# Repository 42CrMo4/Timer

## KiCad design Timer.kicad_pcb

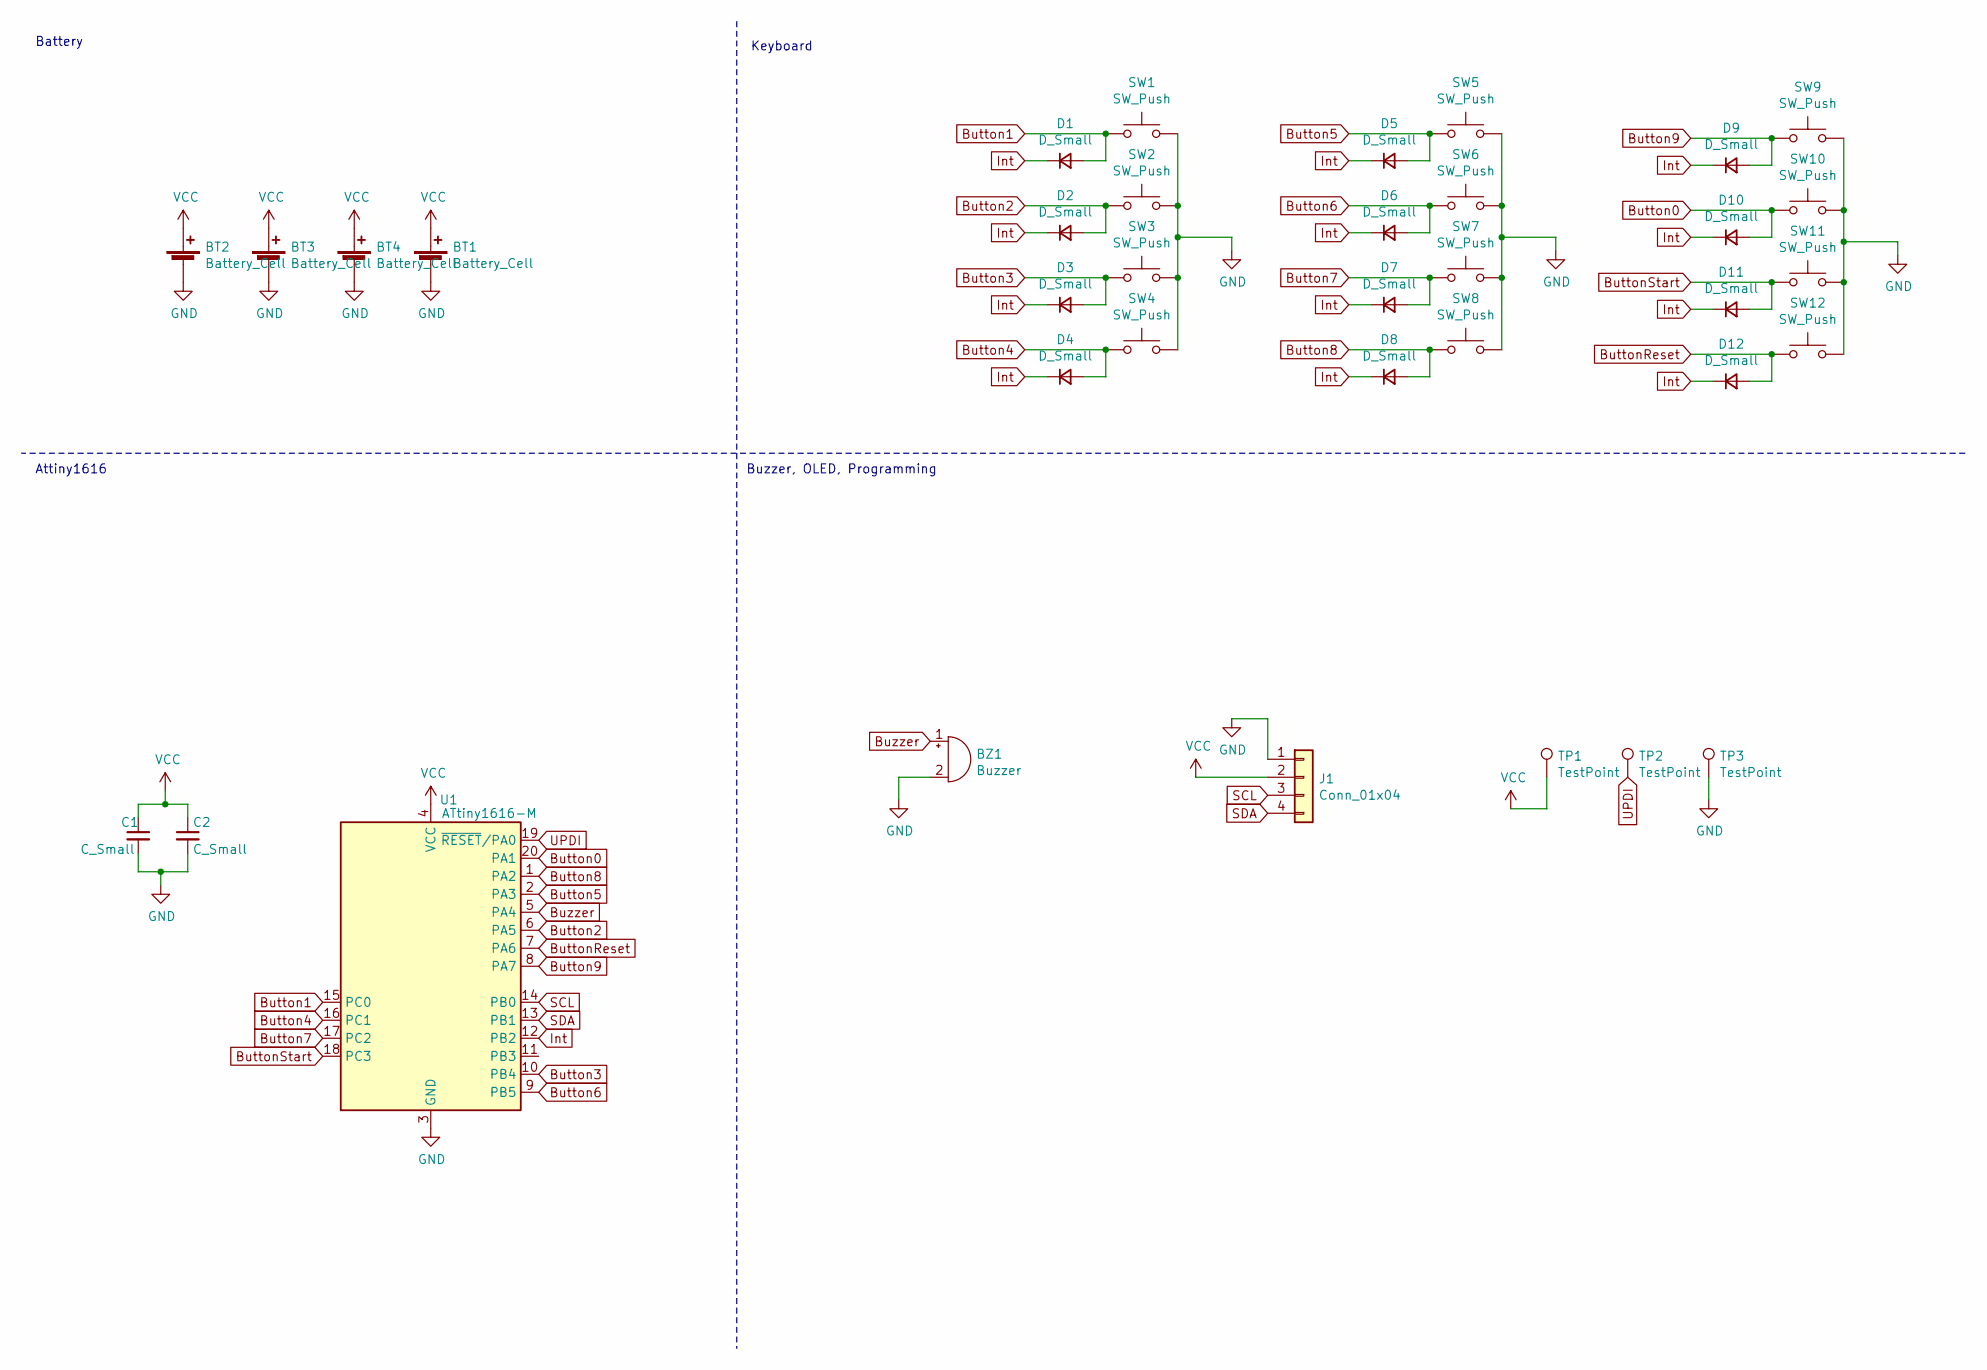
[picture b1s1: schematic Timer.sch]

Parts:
BT1, BT2, BT3, BT4: Battery_Cell; BatteryHolder_3DPrint_1xAAA
BZ1: Buzzer; Buzzer_12x9.5RM7.6
C1, C2: C_Small; C_0805_2012Metric
D1, D2, D3, D4, D5, D6, D7, D8, D9, D10, D11, D12: D_Small; D_0805_2012Metric
J1: Conn_01x04; PinHeader_1x04_P2.54mm_Vertical
SW1, SW2, SW3, SW4, SW5, SW6, SW7, SW8, SW9, SW10, SW11, SW12: SW_Push; SW_Cherry_MX_1.00u_PCB
TP1, TP2, TP3: TestPoint; TestPoint_Pad_D1.5mm
U1: ATtiny1616-M; VQFN-20-1EP_3x3mm_P0.4mm_EP1.7x1.7mm

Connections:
Button0: D10.2 (A), SW10.1, U1.20 (PA1)
Button1: D1.2 (A), SW1.1, U1.15 (PC0)
Button2: D2.2 (A), SW2.1, U1.6 (PA5)
Button3: D3.2 (A), SW3.1, U1.10 (PB4)
Button4: D4.2 (A), SW4.1, U1.16 (PC1)
Button5: D5.2 (A), SW5.1, U1.2 (PA3)
Button6: D6.2 (A), SW6.1, U1.9 (PB5)
Button7: D7.2 (A), SW7.1, U1.17 (PC2)
Button8: D8.2 (A), SW8.1, U1.1 (PA2)
Button9: D9.2 (A), SW9.1, U1.8 (PA7)
ButtonReset: D12.2 (A), SW12.1, U1.7 (PA6)
ButtonStart: D11.2 (A), SW11.1, U1.18 (PC3)
Buzzer: BZ1.1 (-), U1.5 (PA4)
GND: BT1.2 (-), BT2.2 (-), BT3.2 (-), BT4.2 (-), BZ1.2 (+), C1.2, C2.2, J1.1, SW1.2, SW2.2, SW3.2, SW4.2, SW5.2, SW6.2, SW7.2, SW8.2, SW9.2, SW10.2, SW11.2, SW12.2, TP3.1, U1.3 (GND), U1.21 (GND)
Int: D1.1 (K), D2.1 (K), D3.1 (K), D4.1 (K), D5.1 (K), D6.1 (K), D7.1 (K), D8.1 (K), D9.1 (K), D10.1 (K), D11.1 (K), D12.1 (K), U1.12 (PB2)
SCL: J1.3, U1.14 (PB0)
SDA: J1.4, U1.13 (PB1)
UPDI: TP2.1, U1.19 (~RESET~/PA0)
VCC: BT1.1 (+), BT2.1 (+), BT3.1 (+), BT4.1 (+), C1.1, C2.1, J1.2, TP1.1, U1.4 (VCC)

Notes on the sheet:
Battery
Keyboard
Attiny1616
Buzzer, OLED, Programming

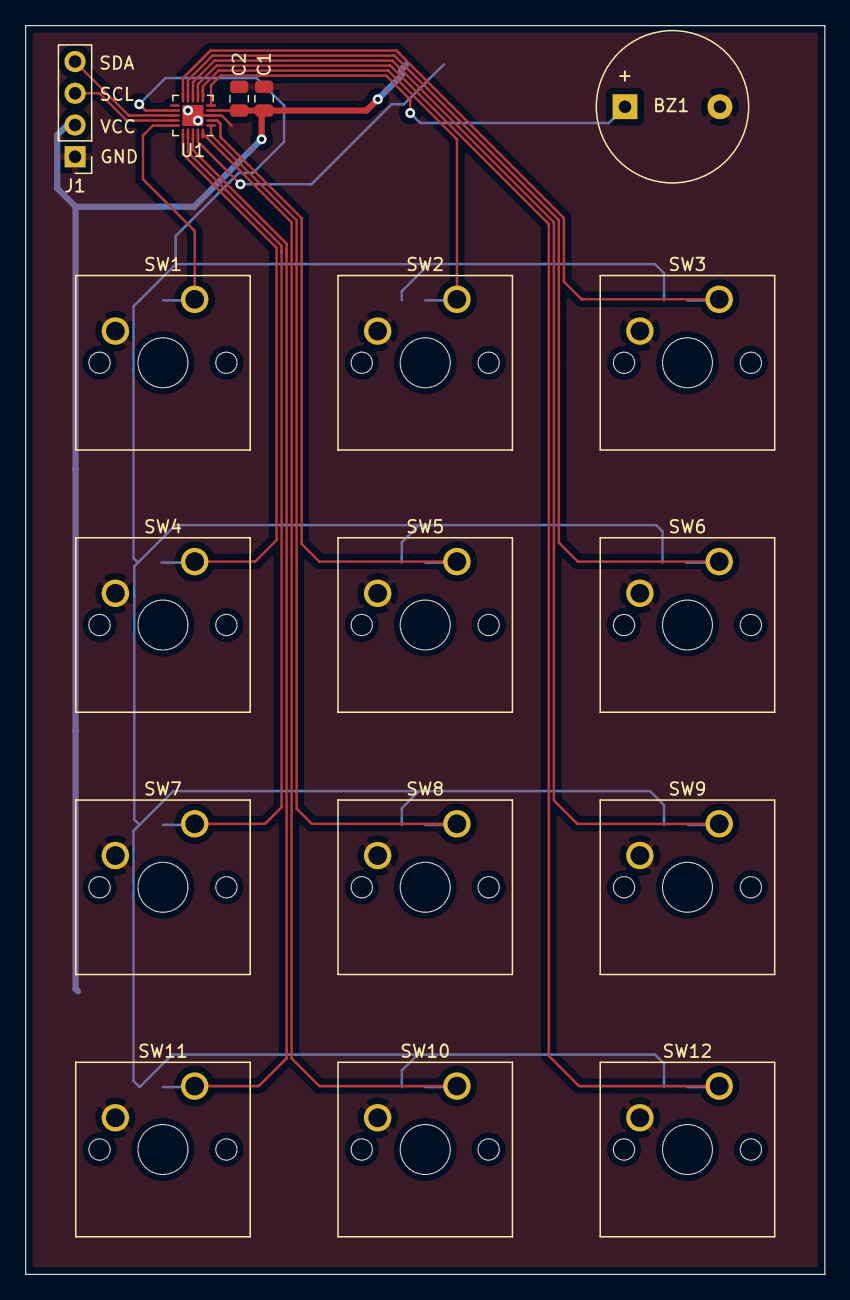
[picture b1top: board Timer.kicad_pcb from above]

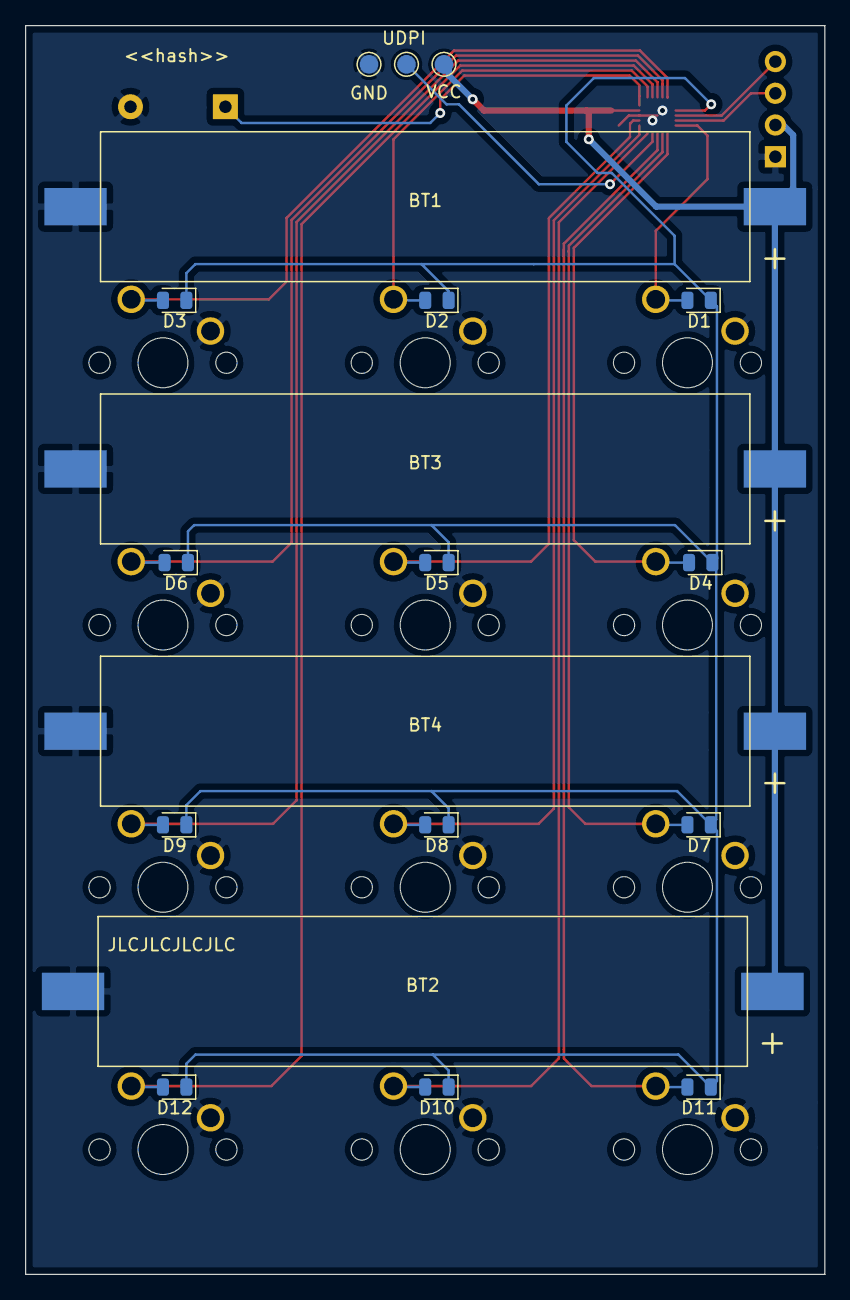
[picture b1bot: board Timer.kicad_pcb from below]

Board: 2 copper layers, 64.0 x 100.0 mm, 36 parts (19 on the bottom side), 19 nets.

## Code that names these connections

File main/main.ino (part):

#include <ezButton.h>
#include <tinyNeoPixel.h>
#define NUMLEDS 22
tinyNeoPixel leds = tinyNeoPixel(NUMLEDS, PIN_PB1, NEO_GRB);
int start_led = 0;

// Setup all Buttons
ezButton button1(PIN_PC0);
ezButton button2(PIN_PA5);
ezButton button3(PIN_PB4);
ezButton button4(PIN_PC1);
ezButton button5(PIN_PA3);
ezButton button6(PIN_PB5);
ezButton button7(PIN_PC2);
ezButton button8(PIN_PA2);
ezButton button9(PIN_PA7);
ezButton button0(PIN_PA1);
ezButton buttonStart(PIN_PC3);
ezButton buttonReset(PIN_PA6);

// int
int h1 = 0;
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
void setup() {
  // Pin configuration SetUp
  pinConfigure(PIN_PA1, (PIN_DIR_INPUT | PIN_PULLUP_ON));
  pinConfigure(PIN_PA2, (PIN_DIR_INPUT | PIN_PULLUP_ON));
  pinConfigure(PIN_PA3, (PIN_DIR_INPUT | PIN_PULLUP_ON));
  pinConfigure(PIN_PA5, (PIN_DIR_INPUT | PIN_PULLUP_ON));
  pinConfigure(PIN_PA6, (PIN_DIR_INPUT | PIN_PULLUP_ON));
  pinConfigure(PIN_PA7, (PIN_DIR_INPUT | PIN_PULLUP_ON));
  pinConfigure(PIN_PB4, (PIN_DIR_INPUT | PIN_PULLUP_ON));
  pinConfigure(PIN_PB5, (PIN_DIR_INPUT | PIN_PULLUP_ON));
  pinConfigure(PIN_PC0, (PIN_DIR_INPUT | PIN_PULLUP_ON));
  pinConfigure(PIN_PC1, (PIN_DIR_INPUT | PIN_PULLUP_ON));
  pinConfigure(PIN_PC2, (PIN_DIR_INPUT | PIN_PULLUP_ON));
  pinConfigure(PIN_PC3, (PIN_DIR_INPUT | PIN_PULLUP_ON));
  pinConfigure(PIN_PA4, (PIN_DIR_OUTPUT));

  delay(100);

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      countown_done = true;
      //      u8x8.clearDisplay();
      leds.clear();
//      digitalWrite(PIN_PA4, HIGH);
//      delay(500);
//      digitalWrite(PIN_PA4, LOW);
      countup();
    }
  }
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
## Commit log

2021-09-25 add SCH/PCB/Req
2021-09-26 add requirements
2021-09-26 add workflow
2021-09-26 test to trigger WF
2021-09-26 update path in WF
2021-09-27 add kiplot file
2021-09-27 WF without path
2021-09-27 WF with Path
2021-09-27 add pcbdraw to WF
2021-09-29 add Silkscreen move Testpoints
2021-09-29 update gnd fill
2021-10-13 add simple Test Sketch
2021-10-13 add oled Test sketch with U8g2
2021-10-13 add timer Sketch
2021-10-14 count over secounds add stopwatch
2021-10-14 refactoring
2021-10-14 refactoring reset
2021-11-01 add battery status
2021-11-01 add all buttons
2021-11-19 formating and comments
2022-01-29 init seven segment display
2022-01-30 remove u8x8 display parts
2022-01-30 remove seconds from showing and hour2 from input
